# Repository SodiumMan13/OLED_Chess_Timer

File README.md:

# OLED_Chess_Timer
A simple OLED chess timer PCB

It is a simple chess timer that I made because I like playing chess with my friend. I thought it would be a good idea to have a fun little chess timer while playing. It is powered by 3 AA batteries in a battery pack and is controlled by a Raspberry Pi Pico as the controller. The two main switches are keyboard switches, and the setting switches are tactile switches.

These are the schematics:

This is the PCB:

This is the render:

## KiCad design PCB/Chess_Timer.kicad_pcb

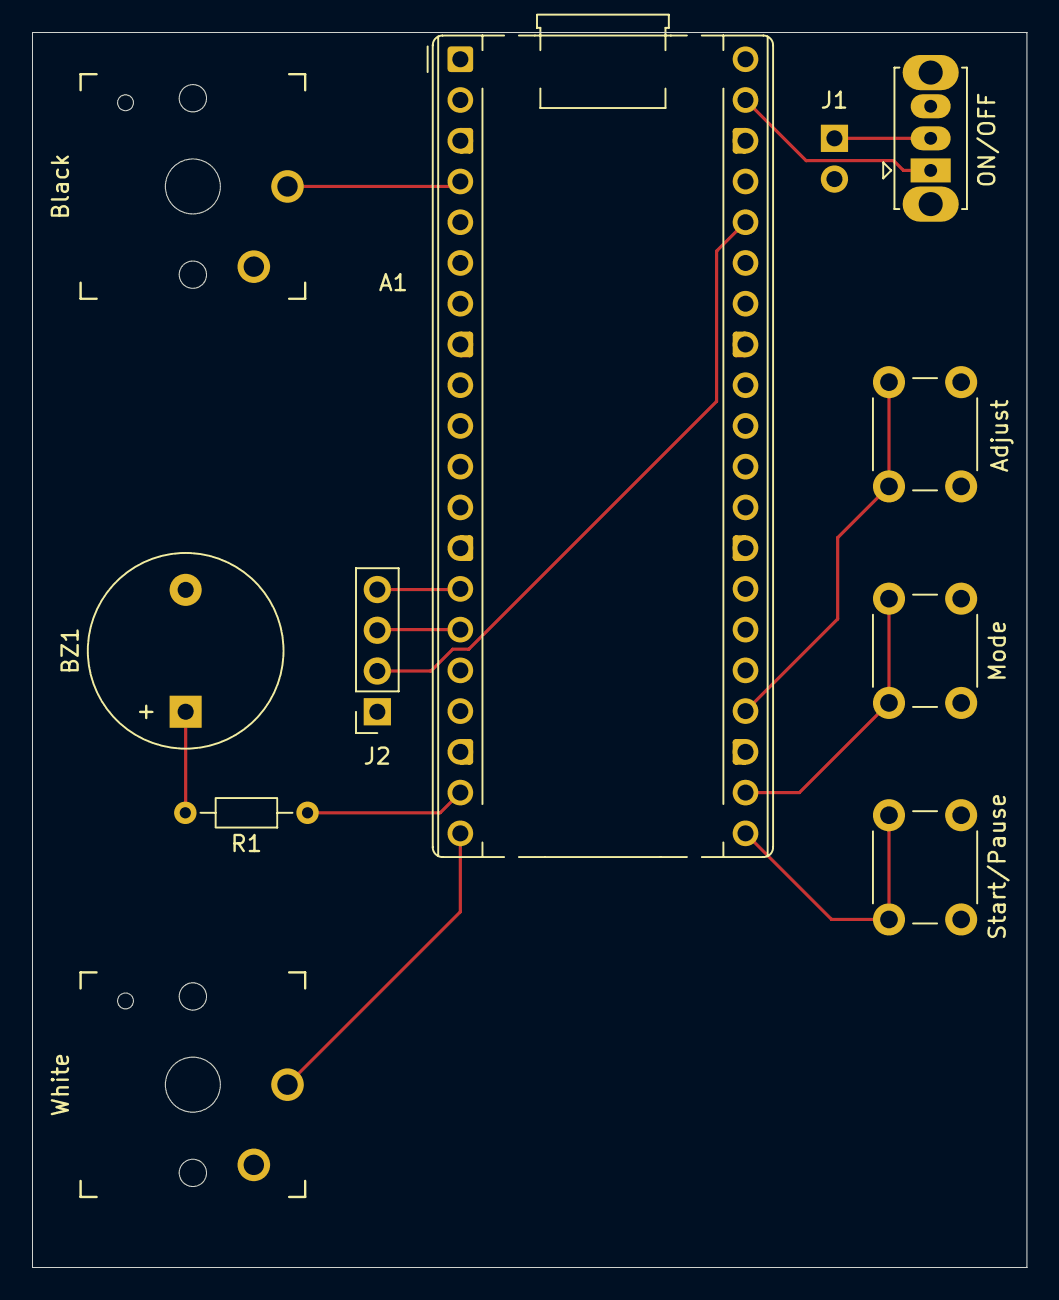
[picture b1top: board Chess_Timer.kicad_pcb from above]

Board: 2 copper layers, 62.0 x 77.0 mm, 11 parts (1 on the bottom side), 13 nets.

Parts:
A1: RaspberryPi_Pico; RaspberryPi_Pico_Common_THT
Adjust: SW_Push; SW_PUSH_6mm_H7.3mm
BZ1: Buzzer; Buzzer_12x9.5RM7.6
Black: SW_Push; Kailh Choc Low-Profile Switches
J1: Conn_01x02_Socket; PinHeader_1x02_P2.54mm_Vertical
J2: Conn_01x04_Socket; PinSocket_1x04_P2.54mm_Vertical
Mode: SW_Push; SW_PUSH_6mm_H7.3mm
ON/OFF: SW_SPDT; SW_Slide_SPDT_Straight_CK_OS102011MS2Q
R1: 220; R_Axial_DIN0204_L3.6mm_D1.6mm_P7.62mm_Horizontal
Start/Pause: SW_Push; SW_PUSH_6mm_H7.3mm
White: SW_Push; Kailh Choc Low-Profile Switches

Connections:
+3.3V: A1.36 (3V3), J2.2
/BLACK: A1.4 (GPIO2), Black.1
/BUZZ: A1.19 (GPIO14), R1.1
/MODE: A1.22 (GPIO17), Mode.1
/PLUS: A1.24 (GPIO18), Adjust.1
/SCL: A1.15 (GPIO11), J2.3
/SDA: A1.14 (GPIO10), J2.4
/START: A1.21 (GPIO16), Start/Pause.1
/Switch: A1.39 (VSYS), ON/OFF.1 (A)
/WHITE: A1.20 (GPIO15), White.1
GND: A1.3 (GND), A1.8 (GND), A1.13 (GND), A1.18 (GND), A1.23 (GND), A1.28 (GND), A1.38 (GND), Adjust.2, BZ1.2 (-), Black.2, J1.2, J2.1, Mode.2, Start/Pause.2, White.2
unnamed: BZ1.1 (+), R1.2
unnamed: J1.1, ON/OFF.2 (B)

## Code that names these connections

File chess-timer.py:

from machine import I2C, Pin, PWM
import ssd1306
import time

# --- HARDWARE PIN MAPPINGS ---
# Display (I2C1: Physical Pin 14 = GP10 for SDA, Physical Pin 15 = GP11 for SCL)
i2c = I2C(1, scl=Pin(11), sda=Pin(10), freq=400000)
display = ssd1306.SSD1306_I2C(128, 64, i2c)

# 5 Buttons (Using internal pull-ups, pressed = 0)
btn_white = Pin(15, Pin.IN, Pin.PULL_UP)  # Pin 20 (GPIO 15) - White player button
btn_black = Pin(2, Pin.IN, Pin.PULL_UP)    # Pin 4  (GPIO 2)  - Black player button
btn_start = Pin(16, Pin.IN, Pin.PULL_UP)  # Pin 21 (GPIO 16) - Start / Pause button
btn_mode  = Pin(17, Pin.IN, Pin.PULL_UP)  # Pin 22 (GPIO 17) - Mode button
btn_adjust = Pin(18, Pin.IN, Pin.PULL_UP) # Pin 24 (GPIO 18) - Adjust button (Plus)

# Buzzer on Physical Pin 19 (GPIO 14)
buzzer = PWM(Pin(14))
buzzer.duty_u16(0)

def beep(freq=2000, duration_ms=100):
    """Play a short piezo beep if buzzer is enabled"""
    if buzzer_enabled:
        buzzer.freq(freq)
        buzzer.duty_u16(32768)
        time.sleep_ms(duration_ms)
        buzzer.duty_u16(0)

def long_buzz(duration_ms=2000):
    """Play a continuous buzz for time out"""
    if buzzer_enabled:
        buzzer.freq(800)
        buzzer.duty_u16(32768)
        time.sleep_ms(duration_ms)
        buzzer.duty_u16(0)

# --- CONFIG & GAME STATES ---
# States: CONFIG_BUZZER, CONFIG_MINUTES, CONFIG_SECONDS, CONFIG_INCREMENT, RUNNING, PAUSED, OVER
ui_state = "CONFIG_BUZZER"

buzzer_enabled = False
set_minutes = 10
set_seconds = 0
set_increment = 0

white_time = 600  # in seconds
black_time = 600  # in seconds
current_turn = "WHITE"

last_tick = time.ticks_ms()
blink_timer = time.ticks_ms()
blink_state = True

def format_time(seconds):
    m = seconds // 60
    s = seconds % 60
    return f"{m:02d}:{s:02d}"

def update_display():
    global blink_state
    display.fill(0)
    
    # Non-blocking blink toggle every 500ms
    if time.ticks_diff(time.ticks_ms(), blink_timer) > 500:
        blink_state = not blink_state
        globals()['blink_timer'] = time.ticks_ms()

    if ui_state == "CONFIG_BUZZER":
        # Show time and flashing buzzer status in top right
        display.text(f"{set_minutes:02d}:{set_seconds:02d}", 10, 25, 1)
        buzz_str = "on" if buzzer_enabled else "off"
        if blink_state:
            display.text(buzz_str, 96, 5, 1)
        display.text("MODE:Next ADJ:Buz", 0, 52, 1)

    elif ui_state == "CONFIG_MINUTES":
        # Minutes flashing
        m_str = f"{set_minutes:02d}" if blink_state else "  "
        display.text(f"{m_str}:{set_seconds:02d}", 10, 25, 1)
        display.text("SET MINUTES", 20, 5, 1)
        display.text("MODE:Next ADJ:+1", 0, 52, 1)

    elif ui_state == "CONFIG_SECONDS":
        # Seconds flashing
        s_str = f"{set_seconds:02d}" if blink_state else "  "
        display.text(f"{set_minutes:02d}:{s_str}", 10, 25, 1)
        display.text("SET SECONDS", 20, 5, 1)
        display.text("MODE:Next ADJ:+10", 0, 52, 1)

    elif ui_state == "CONFIG_INCREMENT":
        # Increment screen (+0 flashing)
        inc_str = f"+{set_increment}"
        if blink_state:
            display.text(inc_str, 48, 25, 1)
        else:
            display.text("  ", 48, 25, 1)
        display.text("INCREMENT (SEC)", 10, 5, 1)
        display.text("START:Play ADJ:+1", 0, 52, 1)

    elif ui_state in ["RUNNING", "PAUSED", "OVER"]:
        w_str = format_time(white_time)
        b_str = format_time(black_time)
        
        if ui_state == "RUNNING":
            w_display = w_str if (current_turn != "WHITE" or blink_state) else "  :  "
            b_display = b_str if (current_turn != "BLACK" or blink_state) else "  :  "
            status = "RUNNING"
        elif ui_state == "PAUSED":
            w_display = w_str
            b_display = b_str
            status = "PAUSED"
        else:
            w_display = w_str
            b_display = b_str
            status = "TIME OUT!"
            
        display.text(f"W: {w_display}", 10, 15, 1)
        display.text(f"B: {b_display}", 10, 35, 1)
        display.text(f"[{status}]", 28, 52, 1)

    display.show()

# Initial draw
update_display()

# --- MAIN LOOP ---
while True:
    update_display()
    
    # 1. START / PAUSE BUTTON
    if not btn_start.value():
        if ui_state in ["CONFIG_BUZZER", "CONFIG_MINUTES", "CONFIG_SECONDS", "CONFIG_INCREMENT"]:
            white_time = (set_minutes * 60) + set_seconds
            black_time = (set_minutes * 60) + set_seconds
            current_turn = "WHITE"
            ui_state = "RUNNING"
            beep(2500, 150)
            last_tick = time.ticks_ms()
            time.sleep(0.3)
        elif ui_state == "RUNNING":
            ui_state = "PAUSED"
            beep(1500, 100)
            time.sleep(0.3)
        elif ui_state == "PAUSED":
            ui_state = "RUNNING"
            beep(2000, 100)
            last_tick = time.ticks_ms() # Reset tick so paused time isn't subtracted
            time.sleep(0.3)
            
    # 2. CONFIG: BUZZER SCREEN
    if ui_state == "CONFIG_BUZZER":
        if not btn_adjust.value():
            buzzer_enabled = not buzzer_enabled
            if buzzer_enabled:
                beep(2000, 50)
            time.sleep(0.3)
            
        elif not btn_mode.value():
            ui_state = "CONFIG_MINUTES"
            beep(1800, 100)
            time.sleep(0.3)

    # 3. CONFIG: MINUTES SCREEN
    elif ui_state == "CONFIG_MINUTES":
        if not btn_adjust.value():
            if 10 <= set_minutes < 15:
                set_minutes += 1
            elif set_minutes == 15:
                set_minutes = 1
            else:
                set_minutes += 1
                if set_minutes > 10:
                    set_minutes = 10
            beep(1500, 40)
            time.sleep(0.3)
            
        elif not btn_mode.value():
            ui_state = "CONFIG_SECONDS"
            beep(1800, 100)
            time.sleep(0.3)

    # 4. CONFIG: SECONDS SCREEN
    elif ui_state == "CONFIG_SECONDS":
        if not btn_adjust.value():
            set_seconds = (set_seconds + 10) % 60
            beep(1600, 40)
            time.sleep(0.3)
            
        elif not btn_mode.value():
            ui_state = "CONFIG_INCREMENT"
            beep(1800, 100)
            time.sleep(0.3)

    # 5. CONFIG: INCREMENT SCREEN
    elif ui_state == "CONFIG_INCREMENT":
        if not btn_adjust.value():
            set_increment = (set_increment + 1) if set_increment < 10 else 0
            beep(1700, 40)
            time.sleep(0.3)
            
        elif not btn_mode.value():
            ui_state = "CONFIG_BUZZER"
            beep(1200, 100)
            time.sleep(0.3)

    # 6. RUNNING GAMEPLAY
    elif ui_state == "RUNNING":
        now = time.ticks_ms()
        
        if not btn_white.value():
            if current_turn == "WHITE":
                white_time += set_increment
                current_turn = "BLACK"
                beep(2000, 60)
                time.sleep(0.2)
                
        if not btn_black.value():
            if current_turn == "BLACK":
                black_time += set_increment
                current_turn = "WHITE"
                beep(2000, 60)
                time.sleep(0.2)
                
        if time.ticks_diff(now, last_tick) >= 1000:
            last_tick = now
            if current_turn == "WHITE":
                if white_time > 0:
                    white_time -= 1
                    if white_time == 0:
                        ui_state = "OVER"
                        long_buzz(2000)
                        ui_state = "CONFIG_BUZZER"
            else:
                if black_time > 0:
                    black_time -= 1
                    if black_time == 0:
                        ui_state = "OVER"
                        long_buzz(2000)
                        ui_state = "CONFIG_BUZZER"

    time.sleep_ms(20)
